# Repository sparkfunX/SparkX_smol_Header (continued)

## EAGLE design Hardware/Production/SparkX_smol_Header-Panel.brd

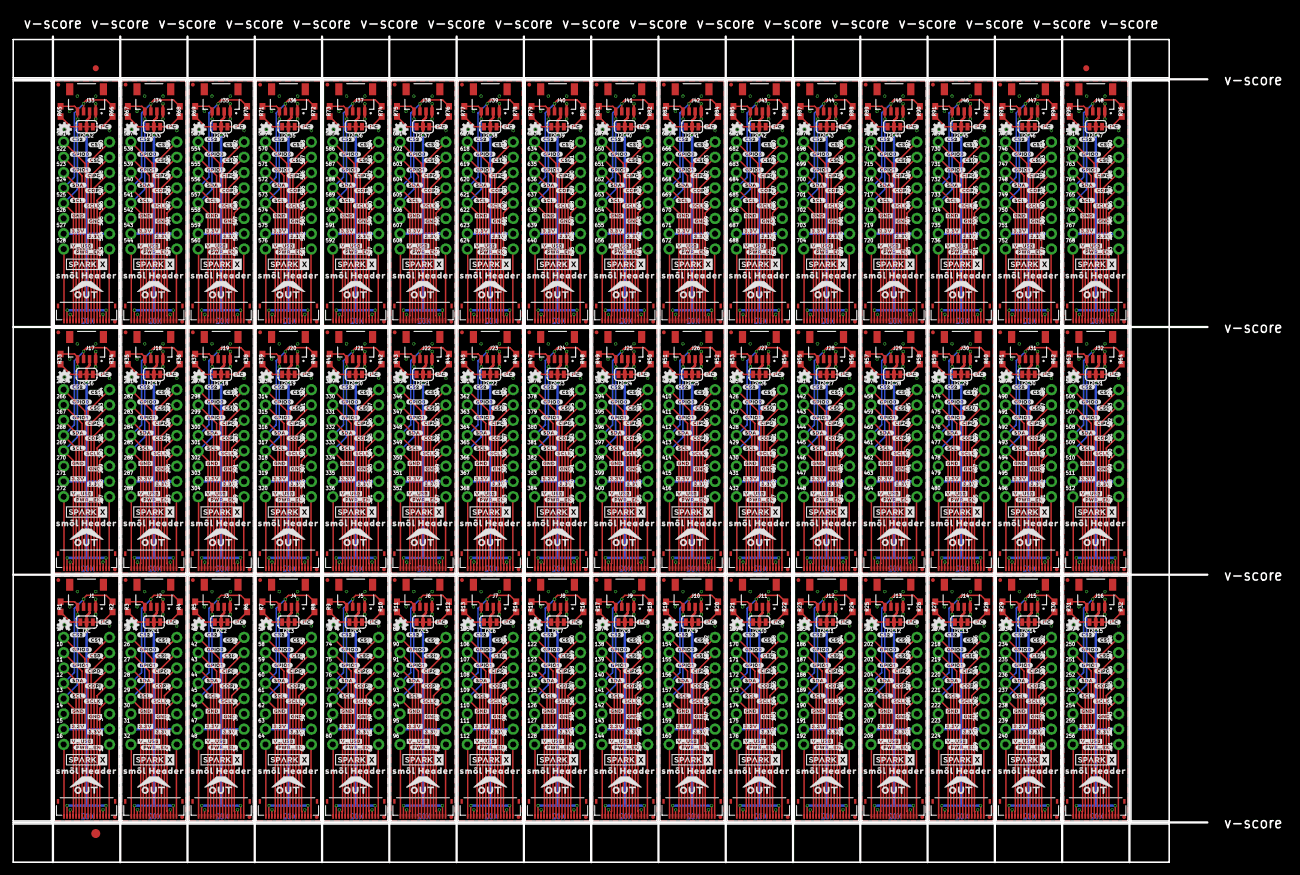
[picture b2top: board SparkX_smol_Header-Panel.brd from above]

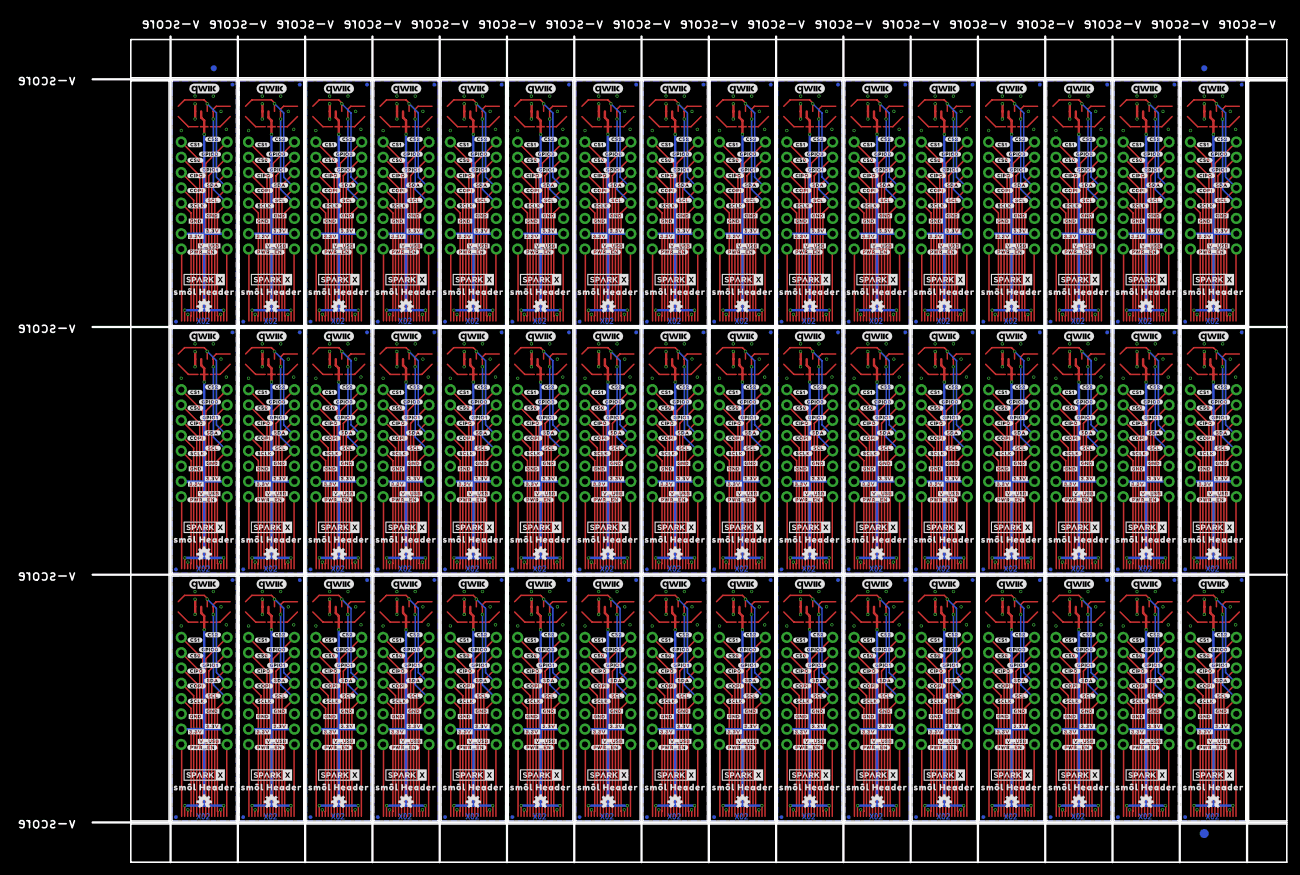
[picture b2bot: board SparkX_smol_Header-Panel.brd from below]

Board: 2 copper layers, 198.4 x 137.2 mm, 3174 parts (1059 on the bottom side), 768 nets.

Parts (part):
1, 2, 3, 4, 5, 6, 7, 8, 9, 10, 11, 12, 13, 14, 15, 16, 17, 18, 19, 20, 21, 22, 23, 24, 25, 26, 27, 28, 29, 30, 31, 32, 33, 34, 35, 36, 37, 38, 39, 40, 41, 42, 43, 44, 45, 46, 47, 48, 49, 50, 51, 52, 53, 54, 55, 56, 57, 58, 59, 60, 61, 62, 63, 64, 65, 66, 67, 68, 69, 70, 71, 72, 73, 74, 75, 76, 77, 78, 79, 80, 81, 82, 83, 84, 85, 86, 87, 88, 89, 90, 91, 92, 93, 94, 95, 96, 97, 98, 99, 100, 101, 102, 103, 104, 105, 106, 107, 108, 109, 110, 111, 112, 113, 114, 115, 116, 117, 118, 119, 120, 121, 122, 123, 124, 125, 126, 127, 128, 129, 130, 131, 132, 133, 134, 135, 136, 137, 138, 139, 140, 141, 142, 143, 144, 145, 146, 147, 148, 149, 150, 151, 152, 153, 154, 155, 156, 157, 158, 159, 160, 161, 162, 163, 164, 165, 166, 167, 168, 169, 170, 171, 172, 173, 174, 175, 176, 177, 178, 179, 180, 181, 182, 183, 184, 185, 186, 187, 188, 189, 190, 191, 192, 193, 194, 195, 196, 197, 198, 199, 200, 201, 202, 203, 204, 205, 206, 207, 208, 209, 210, 211, 212, 213, 214, 215, 216, 217, 218, 219, 220, 221, 222, 223, 224, 225, 226, 227, 228, 229, 230, 231, 232, 233, 234, 235, 236, 237, 238, 239, 240, 241, 242, 243, 244, 245, 246, 247, 248, 249, 250, 251, 252, 253, 254, 255, 256, 257, 258, 259, 260, 261, 262, 263, 264, 265, 266, 267, 268, 269, 270, 271, 272, 273, 274, 275, 276, 277, 278, 279, 280, 281, 282, 283, 284, 285, 286, 287, 288, 289, 290, 291, 292, 293, 294, 295, 296, 297, 298, 299, 300, 301, 302, 303, 304, 305, 306, 307, 308, 309, 310, 311, 312, 313, 314, 315, 316, 317, 318, 319, 320, 321, 322, 323, 324, 325, 326, 327, 328, 329, 330, 331, 332, 333, 334, 335, 336, 337, 338, 339, 340, 341, 342, 343, 344, 345, 346, 347, 348, 349, 350, 351, 352, 353, 354, 355, 356, 357, 358, 359, 360, 361, 362, 363, 364, 365, 366, 367, 368, 369, 370, 371, 372, 373, 374, 375, 376, 377, 378, 379, 380, 381, 382, 383, 384, 385, 386, 387, 388, 389, 390, 391, 392, 393, 394, 395, 396, 397, 398, 399, 400, 401, 402, 403, 404, 405, 406, 407, 408, 409, 410, 411, 412, 413, 414, 415, 416, 417, 418, 419, 420, 421, 422, 423, 424, 425, 426, 427, 428, 429, 430, 431, 432, 433, 434, 435, 436, 437, 438, 439, 440, 441, 442, 443, 444, 445, 446, 447, 448, 449, 450, 451, 452, 453, 454, 455, 456, 457, 458, 459, 460, 461, 462, 463, 464, 465, 466, 467, 468, 469, 470, 471, 472, 473, 474, 475, 476, 477, 478, 479, 480, 481, 482, 483, 484, 485, 486, 487, 488, 489, 490, 491, 492, 493, 494, 495, 496, 497, 498, 499, 500, 501, 502, 503, 504, 505, 506, 507, 508, 509, 510, 511, 512, 513, 514, 515, 516, 517, 518, 519, 520, 521, 522, 523, 524, 525, 526, 527, 528, 529, 530, 531, 532, 533, 534, 535, 536, 537, 538, 539, 540, 541, 542, 543, 544, 545, 546, 547, 548, 549, 550, 551, 552, 553, 554, 555, 556, 557, 558, 559, 560, 561, 562, 563, 564, 565, 566, 567, 568, 569, 570, 571, 572, 573, 574, 575, 576, 577, 578, 579, 580, 581, 582, 583, 584, 585, 586, 587, 588, 589, 590, 591, 592, 593, 594, 595, 596, 597, 598, 599, 600, 601, 602, 603, 604, 605, 606, 607, 608, 609, 610, 611, 612, 613, 614, 615, 616, 617, 618, 619, 620, 621, 622, 623, 624, 625, 626, 627, 628, 629, 630, 631, 632, 633, 634, 635, 636, 637, 638, 639, 640, 641, 642, 643, 644, 645, 646, 647, 648, 649, 650, 651, 652, 653, 654, 655, 656, 657, 658, 659, 660, 661, 662, 663, 664, 665, 666, 667, 668, 669, 670, 671, 672, 673, 674, 675, 676, 677, 678, 679, 680, 681, 682, 683, 684, 685, 686, 687, 688, 689, 690, 691, 692, 693, 694, 695, 696, 697, 698, 699, 700, 701, 702, 703, 704, 705, 706, 707, 708, 709, 710, 711, 712, 713, 714, 715, 716, 717, 718, 719, 720, 721, 722, 723, 724, 725, 726, 727, 728, 729, 730, 731, 732, 733, 734, 735, 736, 737, 738, 739, 740, 741, 742, 743, 744, 745, 746, 747, 748, 749, 750, 751, 752, 753, 754, 755, 756, 757, 758, 759, 760, 761, 762, 763, 764, 765, 766, 767, 768: 1X01_NO_SILK
E$1, E$2, E$3, E$4: FIDUCIAL-1X2
E$5, E$6: FIDUCIAL-1.5X3
FD1, FD2, FD3, FD4, FD5, FD6, FD7, FD8, FD9, FD10, FD11, FD12, FD13, FD14, FD15, FD16, FD17, FD18, FD19, FD20, FD21, FD22, FD23, FD24, FD25, FD26, FD27, FD28, FD29, FD30, FD31, FD32, FD33, FD34, FD35, FD36, FD37, FD38, FD39, FD40, FD41, FD42, FD43, FD44, FD45, FD46, FD47, FD48, FD49, FD50, FD51, FD52, FD53, FD54, FD55, FD56, FD57, FD58, FD59, FD60, FD61, FD62, FD63, FD64, FD65, FD66, FD67, FD68, FD69, FD70, FD71, FD72, FD73, FD74, FD75, FD76, FD77, FD78, FD79, FD80, FD81, FD82, FD83, FD84, FD85, FD86, FD87, FD88, FD89, FD90, FD91, FD92, FD93, FD94, FD95, FD96, FD97, FD98, FD99, FD100, FD101, FD102, FD103, FD104, FD105, FD106, FD107, FD108, FD109, FD110, FD111, FD112, FD113, FD114, FD115, FD116, FD117, FD118, FD119, FD120, FD121, FD122, FD123, FD124, FD125, FD126, FD127, FD128, FD129, FD130, FD131, FD132, FD133, FD134, FD135, FD136, FD137, FD138, FD139, FD140, FD141, FD142, FD143, FD144, FD145, FD146, FD147, FD148, FD149, FD150, FD151, FD152, FD153, FD154, FD155, FD156, FD157, FD158, FD159, FD160, FD161, FD162, FD163, FD164, FD165, FD166, FD167, FD168, FD169, FD170, FD171, FD172, FD173, FD174, FD175, FD176, FD177, FD178, FD179, FD180, FD181, FD182, FD183, FD184, FD185, FD186, FD187, FD188, FD189, FD190, FD191, FD192: FIDUCIALUFIDUCIAL; FIDUCIAL-MICRO
I2C, I2C1, I2C2, I2C3, I2C4, I2C5, I2C6, I2C7, I2C8, I2C9, I2C10, I2C11, I2C12, I2C13, I2C14, I2C15, I2C16, I2C17, I2C18, I2C19, I2C20, I2C21, I2C22, I2C23, I2C24, I2C25, I2C26, I2C27, I2C28, I2C29, I2C30, I2C31, I2C32, I2C33, I2C34, I2C35, I2C36, I2C37, I2C38, I2C39, I2C40, I2C41, I2C42, I2C43, I2C44, I2C45, I2C46, I2C47: JUMPER-SMT_3_2-NC_TRACE_SILK; SMT-JUMPER_3_2-NC_TRACE_SILK
J1, J2, J3, J4, J5, J6, J7, J8, J9, J10, J11, J12, J13, J14, J15, J16, J17, J18, J19, J20, J21, J22, J23, J24, J25, J26, J27, J28, J29, J30, J31, J32, J33, J34, J35, J36, J37, J38, J39, J40, J41, J42, J43, J44, J45, J46, J47, J48: QWIIC_RIGHT_ANGLE; JST04_1MM_RA
LOGO1, LOGO2, LOGO3, LOGO5, LOGO7, LOGO8, LOGO10, LOGO11, LOGO13, LOGO14, LOGO16, LOGO17, LOGO19, LOGO20, LOGO22, LOGO23, LOGO25, LOGO26, LOGO28, LOGO29, LOGO31, LOGO32, LOGO34, LOGO35, LOGO37, LOGO38, LOGO40, LOGO41, LOGO43, LOGO44, LOGO46, LOGO47, LOGO49, LOGO50, LOGO52, LOGO53, LOGO55, LOGO56, LOGO58, LOGO59, LOGO61, LOGO62, LOGO64, LOGO65, LOGO67, LOGO68, LOGO70, LOGO71, LOGO73, LOGO74, LOGO76, LOGO77, LOGO79, LOGO80, LOGO82, LOGO83, LOGO85, LOGO86, LOGO88, LOGO89, LOGO91, LOGO92, LOGO94, LOGO95, LOGO97, LOGO98, LOGO100, LOGO101, LOGO103, LOGO104, LOGO106, LOGO107, LOGO109, LOGO110, LOGO112, LOGO113, LOGO115, LOGO116, LOGO118, LOGO119, LOGO121, LOGO122, LOGO124, LOGO125, LOGO127, LOGO128, LOGO130, LOGO131, LOGO133, LOGO134, LOGO136, LOGO137, LOGO139, LOGO140, LOGO142, LOGO143: OSHW-LOGOMINI; OSHW-LOGO-MINI
LOGO4, LOGO6, LOGO9, LOGO12, LOGO15, LOGO18, LOGO21, LOGO24, LOGO27, LOGO30, LOGO33, LOGO36, LOGO39, LOGO42, LOGO45, LOGO48, LOGO51, LOGO54, LOGO57, LOGO60, LOGO63, LOGO66, LOGO69, LOGO72, LOGO75, LOGO78, LOGO81, LOGO84, LOGO87, LOGO90, LOGO93, LOGO96, LOGO99, LOGO102, LOGO105, LOGO108, LOGO111, LOGO114, LOGO117, LOGO120, LOGO123, LOGO126, LOGO129, LOGO132, LOGO135, LOGO138, LOGO141, LOGO144: QWIIC_LOGO_5MM; QWIIC_5MM
OUT, OUT1, OUT2, OUT3, OUT4, OUT5, OUT6, OUT7, OUT8, OUT9, OUT10, OUT11, OUT12, OUT13, OUT14, OUT15, OUT16, OUT17, OUT18, OUT19, OUT20, OUT21, OUT22, OUT23, OUT24, OUT25, OUT26, OUT27, OUT28, OUT29, OUT30, OUT31, OUT32, OUT33, OUT34, OUT35, OUT36, OUT37, OUT38, OUT39, OUT40, OUT41, OUT42, OUT43, OUT44, OUT45, OUT46, OUT47: FPC_16_0.5MM
R1, R2, R3, R4, R5, R6, R7, R8, R9, R10, R11, R12, R13, R14, R15, R16, R17, R18, R19, R20, R21, R22, R23, R24, R25, R26, R27, R28, R29, R30, R31, R32, R33, R34, R35, R36, R37, R38, R39, R40, R41, R42, R43, R44, R45, R46, R47, R48, R49, R50, R51, R52, R53, R54, R55, R56, R57, R58, R59, R60, R61, R62, R63, R64, R65, R66, R67, R68, R69, R70, R71, R72, R73, R74, R75, R76, R77, R78, R79, R80, R81, R82, R83, R84, R85, R86, R87, R88, R89, R90, R91, R92, R93, R94, R95, R96: 2.2k; 0603
U$1, U$20, U$39, U$57, U$77, U$95, U$115, U$133, U$153, U$171, U$191, U$209, U$229, U$247, U$267, U$285, U$305, U$323, U$343, U$361, U$381, U$399, U$419, U$437, U$457, U$475, U$495, U$513, U$533, U$551, U$571, U$589, U$609, U$627, U$647, U$665, U$685, U$703, U$723, U$741, U$761, U$779, U$799, U$817, U$837, U$855, U$875, U$893, U$913, U$931, U$951, U$969, U$989, U$1007, U$1027, U$1045, U$1065, U$1083, U$1103, U$1121, U$1141, U$1159, U$1179, U$1197, U$1217, U$1235, U$1255, U$1273, U$1293, U$1311, U$1331, U$1349, U$1369, U$1387, U$1407, U$1425, U$1445, U$1463, U$1483, U$1501, U$1521, U$1539, U$1559, U$1577, U$1597, U$1615, U$1635, U$1653, U$1673, U$1691, U$1711, U$1729, U$1749, U$1767, U$1787, U$1805: SPARKX-LOGO3; SPARKX-SMALL
U$2, U$4, U$23, U$24, U$41, U$42, U$59, U$60, U$79, U$80, U$97, U$98, U$117, U$118, U$135, U$136, U$155, U$156, U$173, U$174, U$193, U$194, U$211, U$212, U$231, U$232, U$249, U$250, U$269, U$270, U$287, U$288, U$307, U$308, U$325, U$326, U$345, U$346, U$363, U$364, U$383, U$384, U$401, U$402, U$421, U$422, U$439, U$440, U$459, U$460, U$477, U$478, U$497, U$498, U$515, U$516, U$535, U$536, U$553, U$554, U$573, U$574, U$591, U$592, U$611, U$612, U$629, U$630, U$649, U$650, U$667, U$668, U$687, U$688, U$705, U$706, U$725, U$726, U$743, U$744, U$763, U$764, U$781, U$782, U$801, U$802, U$819, U$820, U$839, U$840, U$857, U$858, U$877, U$878, U$895, U$896, U$915, U$916, U$933, U$934, U$953, U$954, U$971, U$972, U$991, U$992, U$1009, U$1010, U$1029, U$1030, U$1047, U$1048, U$1067, U$1068, U$1085, U$1086, U$1105, U$1106, U$1123, U$1124, U$1143, U$1144, U$1161, U$1162, U$1181, U$1182, U$1199, U$1200, U$1219, U$1220, U$1237, U$1238, U$1257, U$1258, U$1275, U$1276, U$1295, U$1296, U$1313, U$1314, U$1333, U$1334, U$1351, U$1352, U$1371, U$1372, U$1389, U$1390, U$1409, U$1410, U$1427, U$1428, U$1447, U$1448, U$1465, U$1466, U$1485, U$1486, U$1503, U$1504, U$1523, U$1524, U$1541, U$1542, U$1561, U$1562, U$1579, U$1580, U$1599, U$1600, U$1617, U$1618, U$1637, U$1638, U$1655, U$1656, U$1675, U$1676, U$1693, U$1694, U$1713, U$1714, U$1731, U$1732, U$1751, U$1752, U$1769, U$1770, U$1789, U$1790, U$1807, U$1808: #3#3V#0
U$3, U$22, U$40, U$58, U$78, U$96, U$116, U$134, U$154, U$172, U$192, U$210, U$230, U$248, U$268, U$286, U$306, U$324, U$344, U$362, U$382, U$400, U$420, U$438, U$458, U$476, U$496, U$514, U$534, U$552, U$572, U$590, U$610, U$628, U$648, U$666, U$686, U$704, U$724, U$742, U$762, U$780, U$800, U$818, U$838, U$856, U$876, U$894, U$914, U$932, U$952, U$970, U$990, U$1008, U$1028, U$1046, U$1066, U$1084, U$1104, U$1122, U$1142, U$1160, U$1180, U$1198, U$1218, U$1236, U$1256, U$1274, U$1294, U$1312, U$1332, U$1350, U$1370, U$1388, U$1408, U$1426, U$1446, U$1464, U$1484, U$1502, U$1522, U$1540, U$1560, U$1578, U$1598, U$1616, U$1636, U$1654, U$1674, U$1692, U$1712, U$1730, U$1750, U$1768, U$1788, U$1806: #V_USB#0
U$5, U$25, U$43, U$61, U$81, U$99, U$119, U$137, U$157, U$175, U$195, U$213, U$233, U$251, U$271, U$289, U$309, U$327, U$347, U$365, U$385, U$403, U$423, U$441, U$461, U$479, U$499, U$517, U$537, U$555, U$575, U$593, U$613, U$631, U$651, U$669, U$689, U$707, U$727, U$745, U$765, U$783, U$803, U$821, U$841, U$859, U$879, U$897, U$917, U$935, U$955, U$973, U$993, U$1011, U$1031, U$1049, U$1069, U$1087, U$1107, U$1125, U$1145, U$1163, U$1183, U$1201, U$1221, U$1239, U$1259, U$1277, U$1297, U$1315, U$1335, U$1353, U$1373, U$1391, U$1411, U$1429, U$1449, U$1467, U$1487, U$1505, U$1525, U$1543, U$1563, U$1581, U$1601, U$1619, U$1639, U$1657, U$1677, U$1695, U$1715, U$1733, U$1753, U$1771, U$1791, U$1809: #PWR_EN#0
U$6, U$7, U$26, U$27, U$44, U$45, U$62, U$63, U$82, U$83, U$100, U$101, U$120, U$121, U$138, U$139, U$158, U$159, U$176, U$177, U$196, U$197, U$214, U$215, U$234, U$235, U$252, U$253, U$272, U$273, U$290, U$291, U$310, U$311, U$328, U$329, U$348, U$349, U$366, U$367, U$386, U$387, U$404, U$405, U$424, U$425, U$442, U$443, U$462, U$463, U$480, U$481, U$500, U$501, U$518, U$519, U$538, U$539, U$556, U$557, U$576, U$577, U$594, U$595, U$614, U$615, U$632, U$633, U$652, U$653, U$670, U$671, U$690, U$691, U$708, U$709, U$728, U$729, U$746, U$747, U$766, U$767, U$784, U$785, U$804, U$805, U$822, U$823, U$842, U$843, U$860, U$861, U$880, U$881, U$898, U$899, U$918, U$919, U$936, U$937, U$956, U$957, U$974, U$975, U$994, U$995, U$1012, U$1013, U$1032, U$1033, U$1050, U$1051, U$1070, U$1071, U$1088, U$1089, U$1108, U$1109, U$1126, U$1127, U$1146, U$1147, U$1164, U$1165, U$1184, U$1185, U$1202, U$1203, U$1222, U$1223, U$1240, U$1241, U$1260, U$1261, U$1278, U$1279, U$1298, U$1299, U$1316, U$1317, U$1336, U$1337, U$1354, U$1355, U$1374, U$1375, U$1392, U$1393, U$1412, U$1413, U$1430, U$1431, U$1450, U$1451, U$1468, U$1469, U$1488, U$1489, U$1506, U$1507, U$1526, U$1527, U$1544, U$1545, U$1564, U$1565, U$1582, U$1583, U$1602, U$1603, U$1620, U$1621, U$1640, U$1641, U$1658, U$1659, U$1678, U$1679, U$1696, U$1697, U$1716, U$1717, U$1734, U$1735, U$1754, U$1755, U$1772, U$1773, U$1792, U$1793, U$1810, U$1811: #GND#0
U$8, U$28, U$46, U$64, U$84, U$102, U$122, U$140, U$160, U$178, U$198, U$216, U$236, U$254, U$274, U$292, U$312, U$330, U$350, U$368, U$388, U$406, U$426, U$444, U$464, U$482, U$502, U$520, U$540, U$558, U$578, U$596, U$616, U$634, U$654, U$672, U$692, U$710, U$730, U$748, U$768, U$786, U$806, U$824, U$844, U$862, U$882, U$900, U$920, U$938, U$958, U$976, U$996, U$1014, U$1034, U$1052, U$1072, U$1090, U$1110, U$1128, U$1148, U$1166, U$1186, U$1204, U$1224, U$1242, U$1262, U$1280, U$1300, U$1318, U$1338, U$1356, U$1376, U$1394, U$1414, U$1432, U$1452, U$1470, U$1490, U$1508, U$1528, U$1546, U$1566, U$1584, U$1604, U$1622, U$1642, U$1660, U$1680, U$1698, U$1718, U$1736, U$1756, U$1774, U$1794, U$1812: #SCLK#0
U$9, U$38, U$56, U$73, U$94, U$111, U$132, U$149, U$170, U$187, U$208, U$225, U$246, U$263, U$284, U$301, U$322, U$339, U$360, U$377, U$398, U$415, U$436, U$453, U$474, U$491, U$512, U$529, U$550, U$567, U$588, U$605, U$626, U$643, U$664, U$681, U$702, U$719, U$740, U$757, U$778, U$795, U$816, U$833, U$854, U$871, U$892, U$909, U$930, U$947, U$968, U$985, U$1006, U$1023, U$1044, U$1061, U$1082, U$1099, U$1120, U$1137, U$1158, U$1175, U$1196, U$1213, U$1234, U$1251, U$1272, U$1289, U$1310, U$1327, U$1348, U$1365, U$1386, U$1403, U$1424, U$1441, U$1462, U$1479, U$1500, U$1517, U$1538, U$1555, U$1576, U$1593, U$1614, U$1631, U$1652, U$1669, U$1690, U$1707, U$1728, U$1745, U$1766, U$1783, U$1804, U$1821: #SCL#0
U$10, U$29, U$47, U$65, U$85, U$103, U$123, U$141, U$161, U$179, U$199, U$217, U$237, U$255, U$275, U$293, U$313, U$331, U$351, U$369, U$389, U$407, U$427, U$445, U$465, U$483, U$503, U$521, U$541, U$559, U$579, U$597, U$617, U$635, U$655, U$673, U$693, U$711, U$731, U$749, U$769, U$787, U$807, U$825, U$845, U$863, U$883, U$901, U$921, U$939, U$959, U$977, U$997, U$1015, U$1035, U$1053, U$1073, U$1091, U$1111, U$1129, U$1149, U$1167, U$1187, U$1205, U$1225, U$1243, U$1263, U$1281, U$1301, U$1319, U$1339, U$1357, U$1377, U$1395, U$1415, U$1433, U$1453, U$1471, U$1491, U$1509, U$1529, U$1547, U$1567, U$1585, U$1605, U$1623, U$1643, U$1661, U$1681, U$1699, U$1719, U$1737, U$1757, U$1775, U$1795, U$1813: #COPI#0
U$11, U$30, U$48, U$66, U$86, U$104, U$124, U$142, U$162, U$180, U$200, U$218, U$238, U$256, U$276, U$294, U$314, U$332, U$352, U$370, U$390, U$408, U$428, U$446, U$466, U$484, U$504, U$522, U$542, U$560, U$580, U$598, U$618, U$636, U$656, U$674, U$694, U$712, U$732, U$750, U$770, U$788, U$808, U$826, U$846, U$864, U$884, U$902, U$922, U$940, U$960, U$978, U$998, U$1016, U$1036, U$1054, U$1074, U$1092, U$1112, U$1130, U$1150, U$1168, U$1188, U$1206, U$1226, U$1244, U$1264, U$1282, U$1302, U$1320, U$1340, U$1358, U$1378, U$1396, U$1416, U$1434, U$1454, U$1472, U$1492, U$1510, U$1530, U$1548, U$1568, U$1586, U$1606, U$1624, U$1644, U$1662, U$1682, U$1700, U$1720, U$1738, U$1758, U$1776, U$1796, U$1814: #SDA#0
U$12, U$31, U$49, U$67, U$87, U$105, U$125, U$143, U$163, U$181, U$201, U$219, U$239, U$257, U$277, U$295, U$315, U$333, U$353, U$371, U$391, U$409, U$429, U$447, U$467, U$485, U$505, U$523, U$543, U$561, U$581, U$599, U$619, U$637, U$657, U$675, U$695, U$713, U$733, U$751, U$771, U$789, U$809, U$827, U$847, U$865, U$885, U$903, U$923, U$941, U$961, U$979, U$999, U$1017, U$1037, U$1055, U$1075, U$1093, U$1113, U$1131, U$1151, U$1169, U$1189, U$1207, U$1227, U$1245, U$1265, U$1283, U$1303, U$1321, U$1341, U$1359, U$1379, U$1397, U$1417, U$1435, U$1455, U$1473, U$1493, U$1511, U$1531, U$1549, U$1569, U$1587, U$1607, U$1625, U$1645, U$1663, U$1683, U$1701, U$1721, U$1739, U$1759, U$1777, U$1797, U$1815: #CIPO#0
U$13, U$21, U$74, U$75, U$112, U$113, U$150, U$151, U$188, U$189, U$226, U$227, U$264, U$265, U$302, U$303, U$340, U$341, U$378, U$379, U$416, U$417, U$454, U$455, U$492, U$493, U$530, U$531, U$568, U$569, U$606, U$607, U$644, U$645, U$682, U$683, U$720, U$721, U$758, U$759, U$796, U$797, U$834, U$835, U$872, U$873, U$910, U$911, U$948, U$949, U$986, U$987, U$1024, U$1025, U$1062, U$1063, U$1100, U$1101, U$1138, U$1139, U$1176, U$1177, U$1214, U$1215, U$1252, U$1253, U$1290, U$1291, U$1328, U$1329, U$1366, U$1367, U$1404, U$1405, U$1442, U$1443, U$1480, U$1481, U$1518, U$1519, U$1556, U$1557, U$1594, U$1595, U$1632, U$1633, U$1670, U$1671, U$1708, U$1709, U$1746, U$1747, U$1784, U$1785, U$1822, U$1823: SM�L_HEADER0
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
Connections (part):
3.3V: 2.1, 15.1, I2C.2, J1.2, OUT.2, OUT.15
3.3V1: 18.1, 31.1, I2C1.2, J2.2, OUT1.2, OUT1.15
3.3V2: 34.1, 47.1, I2C2.2, J3.2, OUT2.2, OUT2.15
3.3V3: 50.1, 63.1, I2C3.2, J4.2, OUT3.2, OUT3.15
3.3V4: 66.1, 79.1, I2C4.2, J5.2, OUT4.2, OUT4.15
3.3V5: 82.1, 95.1, I2C5.2, J6.2, OUT5.2, OUT5.15
3.3V6: 98.1, 111.1, I2C6.2, J7.2, OUT6.2, OUT6.15
3.3V7: 114.1, 127.1, I2C7.2, J8.2, OUT7.2, OUT7.15
3.3V8: 130.1, 143.1, I2C8.2, J9.2, OUT8.2, OUT8.15
3.3V9: 146.1, 159.1, I2C9.2, J10.2, OUT9.2, OUT9.15
3.3V10: 162.1, 175.1, I2C10.2, J11.2, OUT10.2, OUT10.15
3.3V11: 178.1, 191.1, I2C11.2, J12.2, OUT11.2, OUT11.15
3.3V12: 194.1, 207.1, I2C12.2, J13.2, OUT12.2, OUT12.15
3.3V13: 210.1, 223.1, I2C13.2, J14.2, OUT13.2, OUT13.15
3.3V14: 226.1, 239.1, I2C14.2, J15.2, OUT14.2, OUT14.15
3.3V15: 242.1, 255.1, I2C15.2, J16.2, OUT15.2, OUT15.15
3.3V16: 258.1, 271.1, I2C16.2, J17.2, OUT16.2, OUT16.15
3.3V17: 274.1, 287.1, I2C17.2, J18.2, OUT17.2, OUT17.15
3.3V18: 290.1, 303.1, I2C18.2, J19.2, OUT18.2, OUT18.15
3.3V19: 306.1, 319.1, I2C19.2, J20.2, OUT19.2, OUT19.15
3.3V20: 322.1, 335.1, I2C20.2, J21.2, OUT20.2, OUT20.15
3.3V21: 338.1, 351.1, I2C21.2, J22.2, OUT21.2, OUT21.15
3.3V22: 354.1, 367.1, I2C22.2, J23.2, OUT22.2, OUT22.15
3.3V23: 370.1, 383.1, I2C23.2, J24.2, OUT23.2, OUT23.15
3.3V24: 386.1, 399.1, I2C24.2, J25.2, OUT24.2, OUT24.15
3.3V25: 402.1, 415.1, I2C25.2, J26.2, OUT25.2, OUT25.15
3.3V26: 418.1, 431.1, I2C26.2, J27.2, OUT26.2, OUT26.15
3.3V27: 434.1, 447.1, I2C27.2, J28.2, OUT27.2, OUT27.15
3.3V28: 450.1, 463.1, I2C28.2, J29.2, OUT28.2, OUT28.15
3.3V29: 466.1, 479.1, I2C29.2, J30.2, OUT29.2, OUT29.15
3.3V30: 482.1, 495.1, I2C30.2, J31.2, OUT30.2, OUT30.15
3.3V31: 498.1, 511.1, I2C31.2, J32.2, OUT31.2, OUT31.15
3.3V32: 514.1, 527.1, I2C32.2, J33.2, OUT32.2, OUT32.15
3.3V33: 530.1, 543.1, I2C33.2, J34.2, OUT33.2, OUT33.15
3.3V34: 546.1, 559.1, I2C34.2, J35.2, OUT34.2, OUT34.15
3.3V35: 562.1, 575.1, I2C35.2, J36.2, OUT35.2, OUT35.15
3.3V36: 578.1, 591.1, I2C36.2, J37.2, OUT36.2, OUT36.15
3.3V37: 594.1, 607.1, I2C37.2, J38.2, OUT37.2, OUT37.15
3.3V38: 610.1, 623.1, I2C38.2, J39.2, OUT38.2, OUT38.15
3.3V39: 626.1, 639.1, I2C39.2, J40.2, OUT39.2, OUT39.15
3.3V40: 642.1, 655.1, I2C40.2, J41.2, OUT40.2, OUT40.15
3.3V41: 658.1, 671.1, I2C41.2, J42.2, OUT41.2, OUT41.15
3.3V42: 674.1, 687.1, I2C42.2, J43.2, OUT42.2, OUT42.15
3.3V43: 690.1, 703.1, I2C43.2, J44.2, OUT43.2, OUT43.15
3.3V44: 706.1, 719.1, I2C44.2, J45.2, OUT44.2, OUT44.15
3.3V45: 722.1, 735.1, I2C45.2, J46.2, OUT45.2, OUT45.15
3.3V46: 738.1, 751.1, I2C46.2, J47.2, OUT46.2, OUT46.15
3.3V47: 754.1, 767.1, I2C47.2, J48.2, OUT47.2, OUT47.15
CIPO: 6.1, OUT.6
CIPO1: 22.1, OUT1.6
CIPO2: 38.1, OUT2.6
CIPO3: 54.1, OUT3.6
CIPO4: 70.1, OUT4.6
CIPO5: 86.1, OUT5.6
CIPO6: 102.1, OUT6.6
CIPO7: 118.1, OUT7.6
CIPO8: 134.1, OUT8.6
CIPO9: 150.1, OUT9.6
CIPO10: 166.1, OUT10.6
CIPO11: 182.1, OUT11.6
CIPO12: 198.1, OUT12.6
CIPO13: 214.1, OUT13.6
CIPO14: 230.1, OUT14.6
CIPO15: 246.1, OUT15.6
CIPO16: 262.1, OUT16.6
CIPO17: 278.1, OUT17.6
CIPO18: 294.1, OUT18.6
CIPO19: 310.1, OUT19.6
CIPO20: 326.1, OUT20.6
CIPO21: 342.1, OUT21.6
CIPO22: 358.1, OUT22.6
CIPO23: 374.1, OUT23.6
CIPO24: 390.1, OUT24.6
CIPO25: 406.1, OUT25.6
CIPO26: 422.1, OUT26.6
CIPO27: 438.1, OUT27.6
CIPO28: 454.1, OUT28.6
CIPO29: 470.1, OUT29.6
CIPO30: 486.1, OUT30.6
CIPO31: 502.1, OUT31.6
CIPO32: 518.1, OUT32.6
CIPO33: 534.1, OUT33.6
CIPO34: 550.1, OUT34.6
CIPO35: 566.1, OUT35.6
CIPO36: 582.1, OUT36.6
CIPO37: 598.1, OUT37.6
CIPO38: 614.1, OUT38.6
CIPO39: 630.1, OUT39.6
CIPO40: 646.1, OUT40.6
CIPO41: 662.1, OUT41.6
CIPO42: 678.1, OUT42.6
CIPO43: 694.1, OUT43.6
CIPO44: 710.1, OUT44.6
CIPO45: 726.1, OUT45.6
CIPO46: 742.1, OUT46.6
CIPO47: 758.1, OUT47.6
COPI: 5.1, OUT.5
COPI1: 21.1, OUT1.5
COPI2: 37.1, OUT2.5
COPI3: 53.1, OUT3.5
COPI4: 69.1, OUT4.5
COPI5: 85.1, OUT5.5
COPI6: 101.1, OUT6.5
COPI7: 117.1, OUT7.5
COPI8: 133.1, OUT8.5
COPI9: 149.1, OUT9.5
COPI10: 165.1, OUT10.5
COPI11: 181.1, OUT11.5
COPI12: 197.1, OUT12.5
COPI13: 213.1, OUT13.5
COPI14: 229.1, OUT14.5
COPI15: 245.1, OUT15.5
COPI16: 261.1, OUT16.5
COPI17: 277.1, OUT17.5
COPI18: 293.1, OUT18.5
COPI19: 309.1, OUT19.5
COPI20: 325.1, OUT20.5
COPI21: 341.1, OUT21.5
COPI22: 357.1, OUT22.5
COPI23: 373.1, OUT23.5
COPI24: 389.1, OUT24.5
COPI25: 405.1, OUT25.5
COPI26: 421.1, OUT26.5
COPI27: 437.1, OUT27.5
COPI28: 453.1, OUT28.5
COPI29: 469.1, OUT29.5
COPI30: 485.1, OUT30.5
COPI31: 501.1, OUT31.5
COPI32: 517.1, OUT32.5
COPI33: 533.1, OUT33.5
COPI34: 549.1, OUT34.5
COPI35: 565.1, OUT35.5
COPI36: 581.1, OUT36.5
COPI37: 597.1, OUT37.5
COPI38: 613.1, OUT38.5
COPI39: 629.1, OUT39.5
COPI40: 645.1, OUT40.5
COPI41: 661.1, OUT41.5
COPI42: 677.1, OUT42.5
COPI43: 693.1, OUT43.5
COPI44: 709.1, OUT44.5
COPI45: 725.1, OUT45.5
COPI46: 741.1, OUT46.5
COPI47: 757.1, OUT47.5
CS0: 7.1, OUT.7
CS1: 8.1, OUT.8
CS2: 9.1, OUT.9
CS3: 23.1, OUT1.7
CS4: 24.1, OUT1.8
CS5: 25.1, OUT1.9
CS6: 39.1, OUT2.7
CS7: 40.1, OUT2.8
CS8: 41.1, OUT2.9
CS9: 55.1, OUT3.7
CS10: 56.1, OUT3.8
CS11: 57.1, OUT3.9
CS12: 71.1, OUT4.7
CS13: 72.1, OUT4.8
CS14: 73.1, OUT4.9
CS15: 87.1, OUT5.7
CS16: 88.1, OUT5.8
CS17: 89.1, OUT5.9
CS18: 103.1, OUT6.7
CS19: 104.1, OUT6.8
CS20: 105.1, OUT6.9
CS21: 119.1, OUT7.7
CS22: 120.1, OUT7.8
CS23: 121.1, OUT7.9
CS24: 135.1, OUT8.7
CS25: 136.1, OUT8.8
CS26: 137.1, OUT8.9
CS27: 151.1, OUT9.7
CS28: 152.1, OUT9.8
CS29: 153.1, OUT9.9
CS30: 167.1, OUT10.7
CS31: 168.1, OUT10.8
CS32: 169.1, OUT10.9
CS33: 183.1, OUT11.7
CS34: 184.1, OUT11.8
CS35: 185.1, OUT11.9
CS36: 199.1, OUT12.7
CS37: 200.1, OUT12.8
CS38: 201.1, OUT12.9
CS39: 215.1, OUT13.7
CS40: 216.1, OUT13.8
CS41: 217.1, OUT13.9
CS42: 231.1, OUT14.7
CS43: 232.1, OUT14.8
CS44: 233.1, OUT14.9
CS45: 247.1, OUT15.7
CS46: 248.1, OUT15.8
CS47: 249.1, OUT15.9
CS48: 263.1, OUT16.7
CS49: 264.1, OUT16.8
CS50: 265.1, OUT16.9
CS51: 279.1, OUT17.7
CS52: 280.1, OUT17.8
CS53: 281.1, OUT17.9
CS54: 295.1, OUT18.7
CS55: 296.1, OUT18.8
CS56: 297.1, OUT18.9
CS57: 311.1, OUT19.7
CS58: 312.1, OUT19.8
CS59: 313.1, OUT19.9
CS60: 327.1, OUT20.7
CS61: 328.1, OUT20.8
CS62: 329.1, OUT20.9
CS63: 343.1, OUT21.7
CS64: 344.1, OUT21.8
CS65: 345.1, OUT21.9
CS66: 359.1, OUT22.7
CS67: 360.1, OUT22.8
CS68: 361.1, OUT22.9
CS69: 375.1, OUT23.7
CS70: 376.1, OUT23.8
CS71: 377.1, OUT23.9
CS72: 391.1, OUT24.7
CS73: 392.1, OUT24.8
CS74: 393.1, OUT24.9
CS75: 407.1, OUT25.7
CS76: 408.1, OUT25.8
CS77: 409.1, OUT25.9
CS78: 423.1, OUT26.7
CS79: 424.1, OUT26.8
CS80: 425.1, OUT26.9
CS81: 439.1, OUT27.7
CS82: 440.1, OUT27.8
CS83: 441.1, OUT27.9
CS84: 455.1, OUT28.7
CS85: 456.1, OUT28.8
CS86: 457.1, OUT28.9
CS87: 471.1, OUT29.7
CS88: 472.1, OUT29.8
CS89: 473.1, OUT29.9
CS90: 487.1, OUT30.7
CS91: 488.1, OUT30.8
CS92: 489.1, OUT30.9
CS93: 503.1, OUT31.7
CS94: 504.1, OUT31.8
CS95: 505.1, OUT31.9
CS96: 519.1, OUT32.7
CS97: 520.1, OUT32.8
CS98: 521.1, OUT32.9
CS99: 535.1, OUT33.7
CS100: 536.1, OUT33.8
CS101: 537.1, OUT33.9
CS102: 551.1, OUT34.7
CS103: 552.1, OUT34.8
CS104: 553.1, OUT34.9
CS105: 567.1, OUT35.7
CS106: 568.1, OUT35.8
CS107: 569.1, OUT35.9
CS108: 583.1, OUT36.7
CS109: 584.1, OUT36.8
CS110: 585.1, OUT36.9
CS111: 599.1, OUT37.7
CS112: 600.1, OUT37.8
CS113: 601.1, OUT37.9
CS114: 615.1, OUT38.7
CS115: 616.1, OUT38.8
CS116: 617.1, OUT38.9
CS117: 631.1, OUT39.7
CS118: 632.1, OUT39.8
CS119: 633.1, OUT39.9
CS120: 647.1, OUT40.7
CS121: 648.1, OUT40.8
CS122: 649.1, OUT40.9
CS123: 663.1, OUT41.7
CS124: 664.1, OUT41.8
CS125: 665.1, OUT41.9
CS126: 679.1, OUT42.7
CS127: 680.1, OUT42.8
CS128: 681.1, OUT42.9
CS129: 695.1, OUT43.7
CS130: 696.1, OUT43.8
CS131: 697.1, OUT43.9
CS132: 711.1, OUT44.7
CS133: 712.1, OUT44.8
CS134: 713.1, OUT44.9
CS135: 727.1, OUT45.7
CS136: 728.1, OUT45.8
CS137: 729.1, OUT45.9
CS138: 743.1, OUT46.7
CS139: 744.1, OUT46.8
CS140: 745.1, OUT46.9
CS141: 759.1, OUT47.7
CS142: 760.1, OUT47.8
CS143: 761.1, OUT47.9
GND: 3.1, 14.1, J1.1, OUT.3, OUT.14
GND1: 19.1, 30.1, J2.1, OUT1.3, OUT1.14
GND2: 35.1, 46.1, J3.1, OUT2.3, OUT2.14
GND3: 51.1, 62.1, J4.1, OUT3.3, OUT3.14
GND4: 67.1, 78.1, J5.1, OUT4.3, OUT4.14
GND5: 83.1, 94.1, J6.1, OUT5.3, OUT5.14
GND6: 99.1, 110.1, J7.1, OUT6.3, OUT6.14
GND7: 115.1, 126.1, J8.1, OUT7.3, OUT7.14
GND8: 131.1, 142.1, J9.1, OUT8.3, OUT8.14
GND9: 147.1, 158.1, J10.1, OUT9.3, OUT9.14
GND10: 163.1, 174.1, J11.1, OUT10.3, OUT10.14
GND11: 179.1, 190.1, J12.1, OUT11.3, OUT11.14
GND12: 195.1, 206.1, J13.1, OUT12.3, OUT12.14
GND13: 211.1, 222.1, J14.1, OUT13.3, OUT13.14
GND14: 227.1, 238.1, J15.1, OUT14.3, OUT14.14
GND15: 243.1, 254.1, J16.1, OUT15.3, OUT15.14
GND16: 259.1, 270.1, J17.1, OUT16.3, OUT16.14
GND17: 275.1, 286.1, J18.1, OUT17.3, OUT17.14
GND18: 291.1, 302.1, J19.1, OUT18.3, OUT18.14
GND19: 307.1, 318.1, J20.1, OUT19.3, OUT19.14
GND20: 323.1, 334.1, J21.1, OUT20.3, OUT20.14
GND21: 339.1, 350.1, J22.1, OUT21.3, OUT21.14
GND22: 355.1, 366.1, J23.1, OUT22.3, OUT22.14
GND23: 371.1, 382.1, J24.1, OUT23.3, OUT23.14
GND24: 387.1, 398.1, J25.1, OUT24.3, OUT24.14
GND25: 403.1, 414.1, J26.1, OUT25.3, OUT25.14
GND26: 419.1, 430.1, J27.1, OUT26.3, OUT26.14
GND27: 435.1, 446.1, J28.1, OUT27.3, OUT27.14
GND28: 451.1, 462.1, J29.1, OUT28.3, OUT28.14
GND29: 467.1, 478.1, J30.1, OUT29.3, OUT29.14
GND30: 483.1, 494.1, J31.1, OUT30.3, OUT30.14
GND31: 499.1, 510.1, J32.1, OUT31.3, OUT31.14
GND32: 515.1, 526.1, J33.1, OUT32.3, OUT32.14
GND33: 531.1, 542.1, J34.1, OUT33.3, OUT33.14
GND34: 547.1, 558.1, J35.1, OUT34.3, OUT34.14
GND35: 563.1, 574.1, J36.1, OUT35.3, OUT35.14
GND36: 579.1, 590.1, J37.1, OUT36.3, OUT36.14
GND37: 595.1, 606.1, J38.1, OUT37.3, OUT37.14
GND38: 611.1, 622.1, J39.1, OUT38.3, OUT38.14
GND39: 627.1, 638.1, J40.1, OUT39.3, OUT39.14
GND40: 643.1, 654.1, J41.1, OUT40.3, OUT40.14
GND41: 659.1, 670.1, J42.1, OUT41.3, OUT41.14
GND42: 675.1, 686.1, J43.1, OUT42.3, OUT42.14
GND43: 691.1, 702.1, J44.1, OUT43.3, OUT43.14
GND44: 707.1, 718.1, J45.1, OUT44.3, OUT44.14
GND45: 723.1, 734.1, J46.1, OUT45.3, OUT45.14
GND46: 739.1, 750.1, J47.1, OUT46.3, OUT46.14
GND47: 755.1, 766.1, J48.1, OUT47.3, OUT47.14
GPIO0: 10.1, OUT.10
GPIO1: 11.1, OUT.11
GPIO2: 26.1, OUT1.10
GPIO3: 27.1, OUT1.11
GPIO4: 42.1, OUT2.10
GPIO5: 43.1, OUT2.11
GPIO6: 58.1, OUT3.10
GPIO7: 59.1, OUT3.11
GPIO8: 74.1, OUT4.10
GPIO9: 75.1, OUT4.11
GPIO10: 90.1, OUT5.10
GPIO11: 91.1, OUT5.11
GPIO12: 106.1, OUT6.10
GPIO13: 107.1, OUT6.11
GPIO14: 122.1, OUT7.10
GPIO15: 123.1, OUT7.11
GPIO16: 138.1, OUT8.10
GPIO17: 139.1, OUT8.11
GPIO18: 154.1, OUT9.10
GPIO19: 155.1, OUT9.11
GPIO20: 170.1, OUT10.10
GPIO21: 171.1, OUT10.11
GPIO22: 186.1, OUT11.10
GPIO23: 187.1, OUT11.11
GPIO24: 202.1, OUT12.10
GPIO25: 203.1, OUT12.11
GPIO26: 218.1, OUT13.10
GPIO27: 219.1, OUT13.11
GPIO28: 234.1, OUT14.10
GPIO29: 235.1, OUT14.11
GPIO30: 250.1, OUT15.10
GPIO31: 251.1, OUT15.11
GPIO32: 266.1, OUT16.10
GPIO33: 267.1, OUT16.11
GPIO34: 282.1, OUT17.10
GPIO35: 283.1, OUT17.11
GPIO36: 298.1, OUT18.10
GPIO37: 299.1, OUT18.11
GPIO38: 314.1, OUT19.10
GPIO39: 315.1, OUT19.11
GPIO40: 330.1, OUT20.10
GPIO41: 331.1, OUT20.11
GPIO42: 346.1, OUT21.10
GPIO43: 347.1, OUT21.11
GPIO44: 362.1, OUT22.10
GPIO45: 363.1, OUT22.11
GPIO46: 378.1, OUT23.10
GPIO47: 379.1, OUT23.11
GPIO48: 394.1, OUT24.10
GPIO49: 395.1, OUT24.11
GPIO50: 410.1, OUT25.10
GPIO51: 411.1, OUT25.11
GPIO52: 426.1, OUT26.10
GPIO53: 427.1, OUT26.11
GPIO54: 442.1, OUT27.10
GPIO55: 443.1, OUT27.11
GPIO56: 458.1, OUT28.10
GPIO57: 459.1, OUT28.11
GPIO58: 474.1, OUT29.10
GPIO59: 475.1, OUT29.11
GPIO60: 490.1, OUT30.10
GPIO61: 491.1, OUT30.11
GPIO62: 506.1, OUT31.10
GPIO63: 507.1, OUT31.11
GPIO64: 522.1, OUT32.10
GPIO65: 523.1, OUT32.11
GPIO66: 538.1, OUT33.10
GPIO67: 539.1, OUT33.11
GPIO68: 554.1, OUT34.10
GPIO69: 555.1, OUT34.11
GPIO70: 570.1, OUT35.10
GPIO71: 571.1, OUT35.11
GPIO72: 586.1, OUT36.10
GPIO73: 587.1, OUT36.11
GPIO74: 602.1, OUT37.10
GPIO75: 603.1, OUT37.11
GPIO76: 618.1, OUT38.10
GPIO77: 619.1, OUT38.11
GPIO78: 634.1, OUT39.10
GPIO79: 635.1, OUT39.11
GPIO80: 650.1, OUT40.10
GPIO81: 651.1, OUT40.11
GPIO82: 666.1, OUT41.10
GPIO83: 667.1, OUT41.11
GPIO84: 682.1, OUT42.10
GPIO85: 683.1, OUT42.11
GPIO86: 698.1, OUT43.10
GPIO87: 699.1, OUT43.11
GPIO88: 714.1, OUT44.10
GPIO89: 715.1, OUT44.11
GPIO90: 730.1, OUT45.10
GPIO91: 731.1, OUT45.11
GPIO92: 746.1, OUT46.10
GPIO93: 747.1, OUT46.11
GPIO94: 762.1, OUT47.10
GPIO95: 763.1, OUT47.11
unnamed: I2C.3, R1.2
unnamed: I2C.1, R2.2
unnamed: I2C1.3, R3.2
unnamed: I2C1.1, R4.2
unnamed: I2C2.3, R5.2
unnamed: I2C2.1, R6.2
unnamed: I2C3.3, R7.2
unnamed: I2C3.1, R8.2
unnamed: I2C4.3, R9.2
unnamed: I2C4.1, R10.2
unnamed: I2C5.3, R11.2
unnamed: I2C5.1, R12.2
unnamed: I2C6.3, R13.2
unnamed: I2C6.1, R14.2
unnamed: I2C7.3, R15.2
unnamed: I2C7.1, R16.2
unnamed: I2C8.3, R17.2
unnamed: I2C8.1, R18.2
unnamed: I2C9.3, R19.2
unnamed: I2C9.1, R20.2
unnamed: I2C10.3, R21.2
unnamed: I2C10.1, R22.2
unnamed: I2C11.3, R23.2
unnamed: I2C11.1, R24.2
unnamed: I2C12.3, R25.2
unnamed: I2C12.1, R26.2
unnamed: I2C13.3, R27.2
unnamed: I2C13.1, R28.2
unnamed: I2C14.3, R29.2
unnamed: I2C14.1, R30.2
unnamed: I2C15.3, R31.2
unnamed: I2C15.1, R32.2
unnamed: I2C16.3, R33.2
unnamed: I2C16.1, R34.2
unnamed: I2C17.3, R35.2
unnamed: I2C17.1, R36.2
unnamed: I2C18.3, R37.2
unnamed: I2C18.1, R38.2
unnamed: I2C19.3, R39.2
unnamed: I2C19.1, R40.2
unnamed: I2C20.3, R41.2
unnamed: I2C20.1, R42.2
unnamed: I2C21.3, R43.2
unnamed: I2C21.1, R44.2
unnamed: I2C22.3, R45.2
unnamed: I2C22.1, R46.2
unnamed: I2C23.3, R47.2
unnamed: I2C23.1, R48.2
unnamed: I2C24.3, R49.2
unnamed: I2C24.1, R50.2
unnamed: I2C25.3, R51.2
unnamed: I2C25.1, R52.2
unnamed: I2C26.3, R53.2
unnamed: I2C26.1, R54.2
unnamed: I2C27.3, R55.2
unnamed: I2C27.1, R56.2
unnamed: I2C28.3, R57.2
unnamed: I2C28.1, R58.2
unnamed: I2C29.3, R59.2
unnamed: I2C29.1, R60.2
unnamed: I2C30.3, R61.2
unnamed: I2C30.1, R62.2
unnamed: I2C31.3, R63.2
unnamed: I2C31.1, R64.2
unnamed: I2C32.3, R65.2
unnamed: I2C32.1, R66.2
unnamed: I2C33.3, R67.2
unnamed: I2C33.1, R68.2
unnamed: I2C34.3, R69.2
unnamed: I2C34.1, R70.2
unnamed: I2C35.3, R71.2
unnamed: I2C35.1, R72.2
unnamed: I2C36.3, R73.2
unnamed: I2C36.1, R74.2
unnamed: I2C37.3, R75.2
unnamed: I2C37.1, R76.2
unnamed: I2C38.3, R77.2
unnamed: I2C38.1, R78.2
unnamed: I2C39.3, R79.2
unnamed: I2C39.1, R80.2
unnamed: I2C40.3, R81.2
unnamed: I2C40.1, R82.2
unnamed: I2C41.3, R83.2
unnamed: I2C41.1, R84.2
unnamed: I2C42.3, R85.2
unnamed: I2C42.1, R86.2
unnamed: I2C43.3, R87.2
unnamed: I2C43.1, R88.2
unnamed: I2C44.3, R89.2
unnamed: I2C44.1, R90.2
unnamed: I2C45.3, R91.2
unnamed: I2C45.1, R92.2
unnamed: I2C46.3, R93.2
unnamed: I2C46.1, R94.2
unnamed: I2C47.3, R95.2
unnamed: I2C47.1, R96.2
PROC_PWR_EN: 1.1, OUT.1
PROC_PWR_EN1: 17.1, OUT1.1
PROC_PWR_EN2: 33.1, OUT2.1
PROC_PWR_EN3: 49.1, OUT3.1
PROC_PWR_EN4: 65.1, OUT4.1
PROC_PWR_EN5: 81.1, OUT5.1
PROC_PWR_EN6: 97.1, OUT6.1
PROC_PWR_EN7: 113.1, OUT7.1
PROC_PWR_EN8: 129.1, OUT8.1
PROC_PWR_EN9: 145.1, OUT9.1
PROC_PWR_EN10: 161.1, OUT10.1
PROC_PWR_EN11: 177.1, OUT11.1
PROC_PWR_EN12: 193.1, OUT12.1
PROC_PWR_EN13: 209.1, OUT13.1
PROC_PWR_EN14: 225.1, OUT14.1
PROC_PWR_EN15: 241.1, OUT15.1
PROC_PWR_EN16: 257.1, OUT16.1
PROC_PWR_EN17: 273.1, OUT17.1
PROC_PWR_EN18: 289.1, OUT18.1
PROC_PWR_EN19: 305.1, OUT19.1
PROC_PWR_EN20: 321.1, OUT20.1
PROC_PWR_EN21: 337.1, OUT21.1
PROC_PWR_EN22: 353.1, OUT22.1
PROC_PWR_EN23: 369.1, OUT23.1
PROC_PWR_EN24: 385.1, OUT24.1
PROC_PWR_EN25: 401.1, OUT25.1
PROC_PWR_EN26: 417.1, OUT26.1
PROC_PWR_EN27: 433.1, OUT27.1
PROC_PWR_EN28: 449.1, OUT28.1
PROC_PWR_EN29: 465.1, OUT29.1
PROC_PWR_EN30: 481.1, OUT30.1
PROC_PWR_EN31: 497.1, OUT31.1
PROC_PWR_EN32: 513.1, OUT32.1
PROC_PWR_EN33: 529.1, OUT33.1
PROC_PWR_EN34: 545.1, OUT34.1
PROC_PWR_EN35: 561.1, OUT35.1
PROC_PWR_EN36: 577.1, OUT36.1
PROC_PWR_EN37: 593.1, OUT37.1
PROC_PWR_EN38: 609.1, OUT38.1
PROC_PWR_EN39: 625.1, OUT39.1
PROC_PWR_EN40: 641.1, OUT40.1
PROC_PWR_EN41: 657.1, OUT41.1
PROC_PWR_EN42: 673.1, OUT42.1
PROC_PWR_EN43: 689.1, OUT43.1
PROC_PWR_EN44: 705.1, OUT44.1
PROC_PWR_EN45: 721.1, OUT45.1
PROC_PWR_EN46: 737.1, OUT46.1
PROC_PWR_EN47: 753.1, OUT47.1
SCL: 13.1, J1.4, OUT.13, R1.1
SCL1: 29.1, J2.4, OUT1.13, R3.1
SCL2: 45.1, J3.4, OUT2.13, R5.1
SCL3: 61.1, J4.4, OUT3.13, R7.1
SCL4: 77.1, J5.4, OUT4.13, R9.1
SCL5: 93.1, J6.4, OUT5.13, R11.1
SCL6: 109.1, J7.4, OUT6.13, R13.1
SCL7: 125.1, J8.4, OUT7.13, R15.1
SCL8: 141.1, J9.4, OUT8.13, R17.1
SCL9: 157.1, J10.4, OUT9.13, R19.1
SCL10: 173.1, J11.4, OUT10.13, R21.1
SCL11: 189.1, J12.4, OUT11.13, R23.1
SCL12: 205.1, J13.4, OUT12.13, R25.1
SCL13: 221.1, J14.4, OUT13.13, R27.1
SCL14: 237.1, J15.4, OUT14.13, R29.1
SCL15: 253.1, J16.4, OUT15.13, R31.1
SCL16: 269.1, J17.4, OUT16.13, R33.1
SCL17: 285.1, J18.4, OUT17.13, R35.1
SCL18: 301.1, J19.4, OUT18.13, R37.1
SCL19: 317.1, J20.4, OUT19.13, R39.1
SCL20: 333.1, J21.4, OUT20.13, R41.1
SCL21: 349.1, J22.4, OUT21.13, R43.1
SCL22: 365.1, J23.4, OUT22.13, R45.1
SCL23: 381.1, J24.4, OUT23.13, R47.1
SCL24: 397.1, J25.4, OUT24.13, R49.1
SCL25: 413.1, J26.4, OUT25.13, R51.1
SCL26: 429.1, J27.4, OUT26.13, R53.1
SCL27: 445.1, J28.4, OUT27.13, R55.1
SCL28: 461.1, J29.4, OUT28.13, R57.1
SCL29: 477.1, J30.4, OUT29.13, R59.1
SCL30: 493.1, J31.4, OUT30.13, R61.1
SCL31: 509.1, J32.4, OUT31.13, R63.1
SCL32: 525.1, J33.4, OUT32.13, R65.1
SCL33: 541.1, J34.4, OUT33.13, R67.1
SCL34: 557.1, J35.4, OUT34.13, R69.1
SCL35: 573.1, J36.4, OUT35.13, R71.1
SCL36: 589.1, J37.4, OUT36.13, R73.1
SCL37: 605.1, J38.4, OUT37.13, R75.1
SCL38: 621.1, J39.4, OUT38.13, R77.1
SCL39: 637.1, J40.4, OUT39.13, R79.1
SCL40: 653.1, J41.4, OUT40.13, R81.1
SCL41: 669.1, J42.4, OUT41.13, R83.1
SCL42: 685.1, J43.4, OUT42.13, R85.1
SCL43: 701.1, J44.4, OUT43.13, R87.1
SCL44: 717.1, J45.4, OUT44.13, R89.1
SCL45: 733.1, J46.4, OUT45.13, R91.1
SCL46: 749.1, J47.4, OUT46.13, R93.1
SCL47: 765.1, J48.4, OUT47.13, R95.1
SCLK: 4.1, OUT.4
SCLK1: 20.1, OUT1.4
SCLK2: 36.1, OUT2.4
SCLK3: 52.1, OUT3.4
SCLK4: 68.1, OUT4.4
SCLK5: 84.1, OUT5.4
SCLK6: 100.1, OUT6.4
SCLK7: 116.1, OUT7.4
SCLK8: 132.1, OUT8.4
SCLK9: 148.1, OUT9.4
SCLK10: 164.1, OUT10.4
SCLK11: 180.1, OUT11.4
SCLK12: 196.1, OUT12.4
SCLK13: 212.1, OUT13.4
SCLK14: 228.1, OUT14.4
SCLK15: 244.1, OUT15.4
SCLK16: 260.1, OUT16.4
SCLK17: 276.1, OUT17.4
SCLK18: 292.1, OUT18.4
SCLK19: 308.1, OUT19.4
SCLK20: 324.1, OUT20.4
SCLK21: 340.1, OUT21.4
SCLK22: 356.1, OUT22.4
SCLK23: 372.1, OUT23.4
SCLK24: 388.1, OUT24.4
SCLK25: 404.1, OUT25.4
SCLK26: 420.1, OUT26.4
SCLK27: 436.1, OUT27.4
SCLK28: 452.1, OUT28.4
SCLK29: 468.1, OUT29.4
SCLK30: 484.1, OUT30.4
SCLK31: 500.1, OUT31.4
SCLK32: 516.1, OUT32.4
SCLK33: 532.1, OUT33.4
SCLK34: 548.1, OUT34.4
SCLK35: 564.1, OUT35.4
SCLK36: 580.1, OUT36.4
SCLK37: 596.1, OUT37.4
SCLK38: 612.1, OUT38.4
SCLK39: 628.1, OUT39.4
SCLK40: 644.1, OUT40.4
SCLK41: 660.1, OUT41.4
SCLK42: 676.1, OUT42.4
SCLK43: 692.1, OUT43.4
SCLK44: 708.1, OUT44.4
SCLK45: 724.1, OUT45.4
SCLK46: 740.1, OUT46.4
SCLK47: 756.1, OUT47.4
SDA: 12.1, J1.3, OUT.12, R2.1
SDA1: 28.1, J2.3, OUT1.12, R4.1
SDA2: 44.1, J3.3, OUT2.12, R6.1
SDA3: 60.1, J4.3, OUT3.12, R8.1
SDA4: 76.1, J5.3, OUT4.12, R10.1
SDA5: 92.1, J6.3, OUT5.12, R12.1
SDA6: 108.1, J7.3, OUT6.12, R14.1
SDA7: 124.1, J8.3, OUT7.12, R16.1
SDA8: 140.1, J9.3, OUT8.12, R18.1
SDA9: 156.1, J10.3, OUT9.12, R20.1
SDA10: 172.1, J11.3, OUT10.12, R22.1
SDA11: 188.1, J12.3, OUT11.12, R24.1
SDA12: 204.1, J13.3, OUT12.12, R26.1
SDA13: 220.1, J14.3, OUT13.12, R28.1
SDA14: 236.1, J15.3, OUT14.12, R30.1
SDA15: 252.1, J16.3, OUT15.12, R32.1
SDA16: 268.1, J17.3, OUT16.12, R34.1
SDA17: 284.1, J18.3, OUT17.12, R36.1
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
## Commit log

2021-05-04 Add bottom silk
2021-05-27 Gapless production panel
2021-06-09 Update 16-way FPC Connector
2021-08-18 X02 - add smol branding
2021-08-19 Update smôl logo
2021-08-20 Change EZ to smôl on schematic
2021-10-28 Add SKU and product image
